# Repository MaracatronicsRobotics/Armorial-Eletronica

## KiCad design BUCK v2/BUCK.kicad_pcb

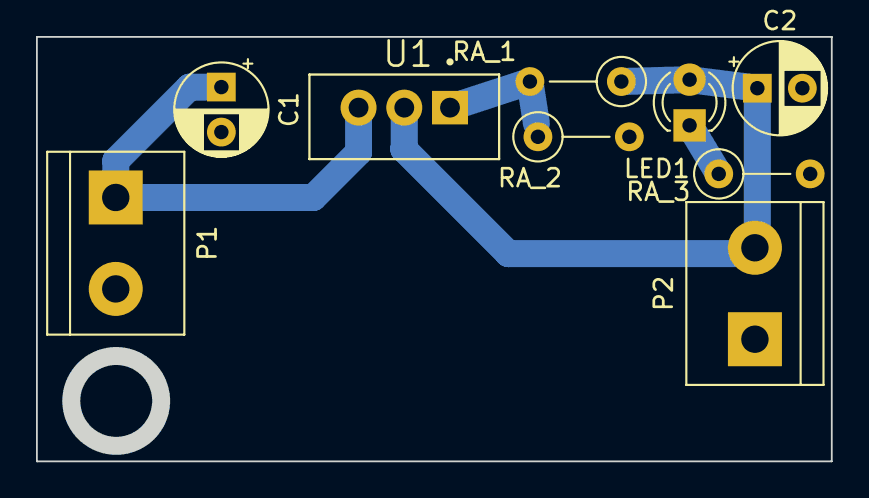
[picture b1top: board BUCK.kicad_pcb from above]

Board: 2 copper layers, 44.2 x 23.6 mm, 9 parts (0 on the bottom side), 5 nets.

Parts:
C1, C2: 100u; CP_Radial_D5.0mm_P2.50mm
LED1: LED; LED_D3.0mm
P1, P2: 282837-2; TerminalBlock_bornier-2_P5.08mm
RA_1: 220; R_Axial_DIN0207_L6.3mm_D2.5mm_P5.08mm_Vertical
RA_2: 1.2k; R_Axial_DIN0207_L6.3mm_D2.5mm_P5.08mm_Vertical
RA_3: 1k; R_Axial_DIN0207_L6.3mm_D2.5mm_P5.08mm_Vertical
U1: LM338T; TO254P1054X470X1955-3

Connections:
8V: C2.1, LED1.2 (A), P2.2, RA_1.1, U1.2 (VOUT)
18V: C1.1, P1.1, U1.3 (VIN)
GND: C1.2, C2.2, P1.2, P2.1, RA_2.2, RA_3.2
unnamed: LED1.1 (K), RA_3.1
unnamed: RA_1.2, RA_2.1, U1.1 (ADJ)

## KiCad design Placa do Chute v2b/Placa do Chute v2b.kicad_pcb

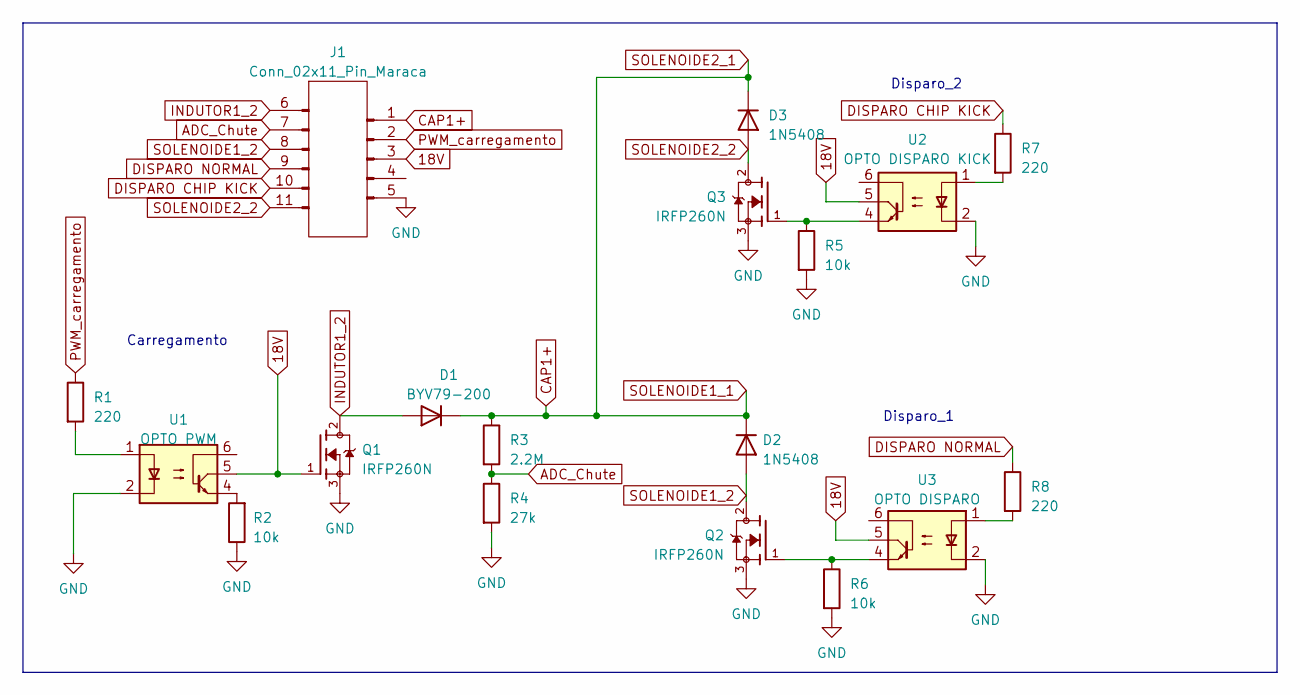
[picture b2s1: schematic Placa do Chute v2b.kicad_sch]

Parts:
D1: BYV79-200; TO-220-2_Vertical
D2, D3: 1N5408; D_DO-201AD_P15.24mm_Horizontal
J1: Conn_02x11_Pin_Maraca; Conn_2x11_Maraca_Chute
Q1, Q2, Q3: IRFP260N; TO545P1560X500X2460-3 90d; PARTREV 08/18/10
R1, R7, R8: 220; R_Axial_DIN0207_L6.3mm_D2.5mm_P10.16mm_Horizontal
R2, R5, R6: 10k; R_Axial_DIN0207_L6.3mm_D2.5mm_P10.16mm_Horizontal
R3: 2.2M; R_Axial_DIN0207_L6.3mm_D2.5mm_P10.16mm_Horizontal
R4: 27k; R_Axial_DIN0207_L6.3mm_D2.5mm_P10.16mm_Horizontal
U1: OPTO PWM; DIP-6_W7.62mm
U2: OPTO DISPARO KICK; DIP-6_W7.62mm
U3: OPTO DISPARO; DIP-6_W7.62mm

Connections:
18V: J1.3, Q1.1, U1.5, U2.5, U3.5
ADC_Chute: J1.7, R3.2, R4.1
CAP1+: D1.1 (K), D2.1 (K), D3.1 (K), J1.1, R3.1
DISPARO CHIP KICK: J1.10, R7.1
DISPARO NORMAL: J1.9, R8.1
GND: J1.5, Q1.3, Q2.3, Q3.3, R2.1, R4.2, R5.2, R6.2, U1.2, U2.2, U3.2
INDUTOR1_2: D1.2 (A), J1.6, Q1.2
unnamed: Q2.1, R6.1, U3.4
unnamed: Q3.1, R5.1, U2.4
unnamed: R1.2, U1.1
unnamed: R2.2, U1.4
unnamed: R7.2, U2.1
unnamed: R8.2, U3.1
PWM_carregamento: J1.2, R1.1
SOLENOIDE1_2: D2.2 (A), J1.8, Q2.2
SOLENOIDE2_2: D3.2 (A), J1.11, Q3.2

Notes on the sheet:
Disparo_2
Carregamento
Disparo_1

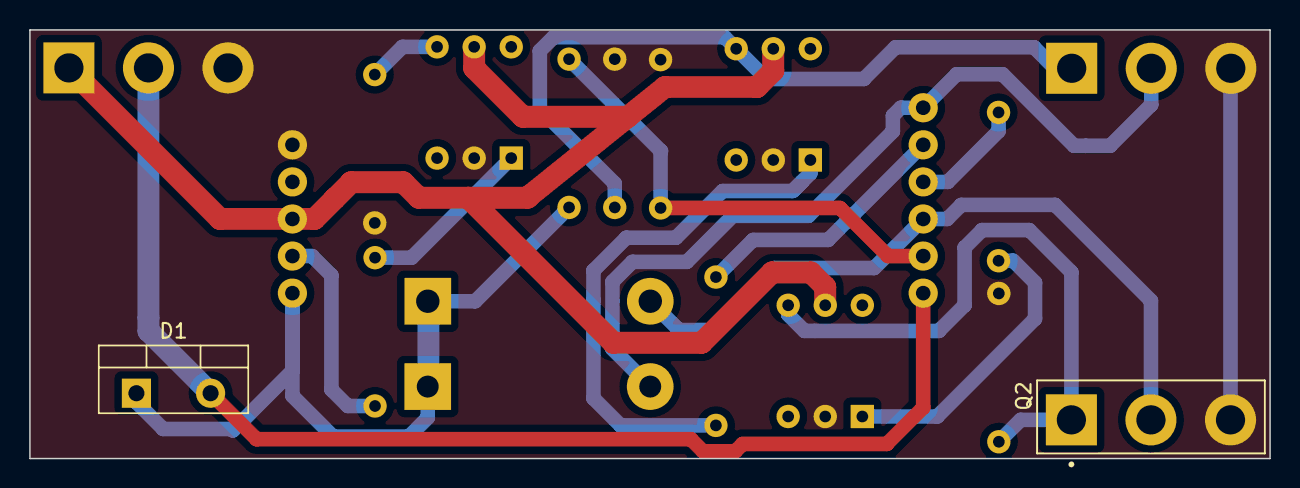
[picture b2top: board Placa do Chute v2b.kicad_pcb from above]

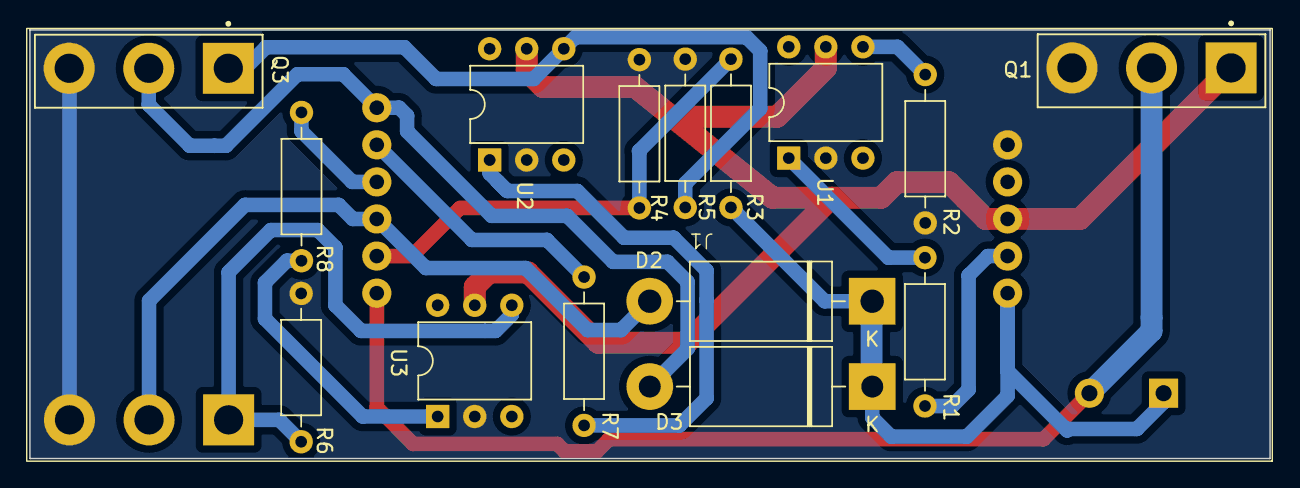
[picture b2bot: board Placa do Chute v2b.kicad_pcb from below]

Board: 2 copper layers, 84.9 x 29.4 mm, 18 parts (16 on the bottom side), 16 nets.

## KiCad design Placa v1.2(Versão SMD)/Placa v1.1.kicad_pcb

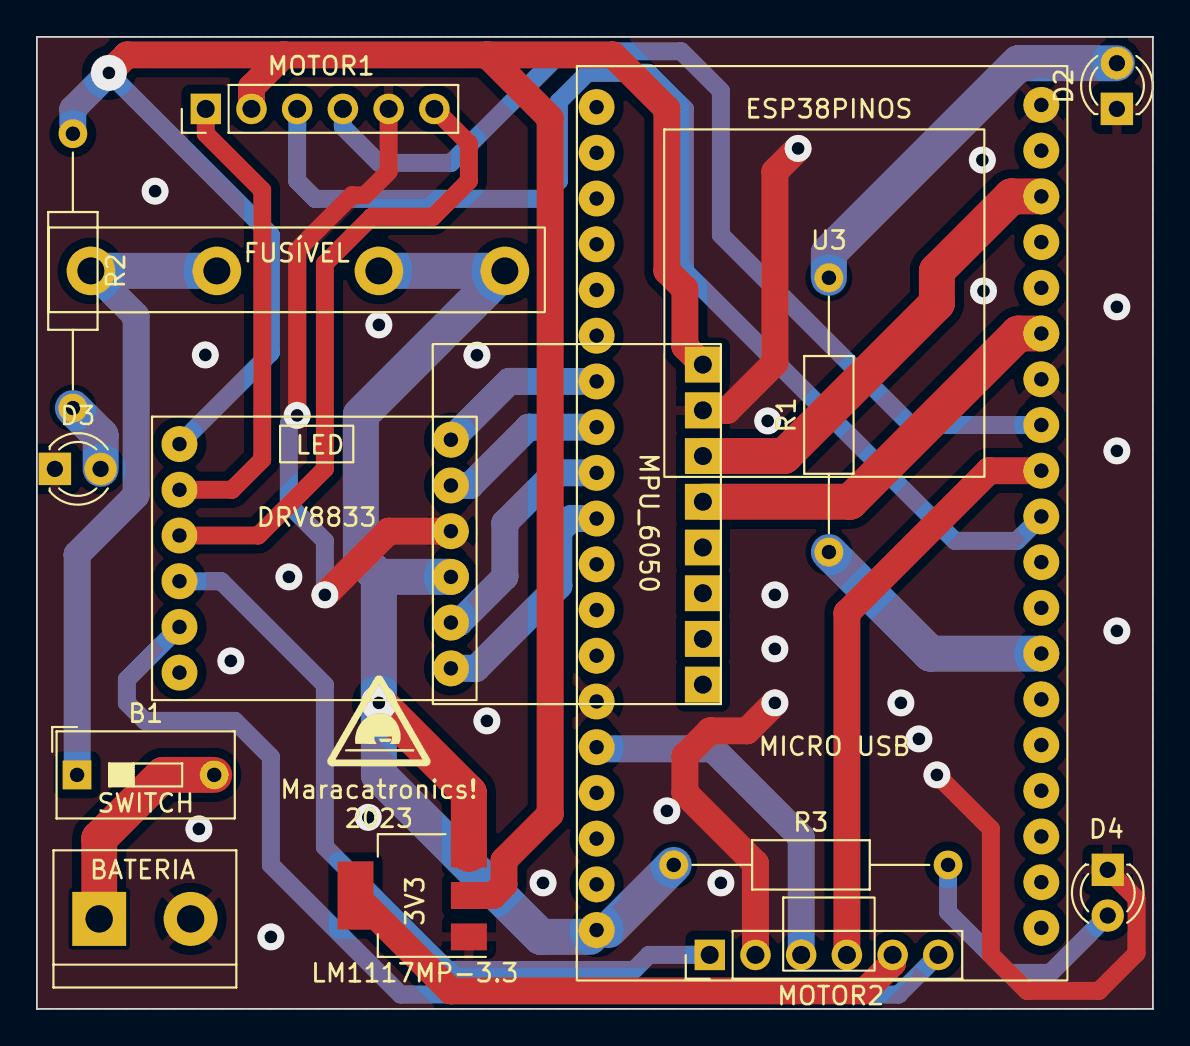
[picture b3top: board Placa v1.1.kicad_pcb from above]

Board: 2 copper layers, 62.0 x 54.0 mm, 15 parts (0 on the bottom side), 21 nets.

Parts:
3V3: LM1117MP-3.3; SOT-223-3_TabPin2
B1: SWITCH; SW_DIP_SPSTx01_Slide_9.78x4.72mm_W7.62mm_P2.54mm
BATERIA: Conn_01x02_Male; TerminalBlock_bornier-2_P5.08mm
D2, D3, D4: LED; LED_D3.0mm
DRV8833: DRV8833
FUSÍVEL: Fusivel; FUSIVEL
MOTOR1, MOTOR2: Conn_01x06_Male; PinHeader_1x06_P2.54mm_Vertical
MPU6050: MPU_6050; MPU 6050
R1, R2, R3: R_US; R_Axial_DIN0207_L6.3mm_D2.5mm_P15.24mm_Horizontal
U3: ESP38PINOS; ESP 38 PINOS

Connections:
3v3: 3V3.2 (VO), DRV8833.A0 (EEP), MOTOR1.2, MOTOR2.5, MPU6050.A0 (VCC), R2.1
7.4V: 3V3.3 (VI), B1.1, DRV8833.A9 (VCC), FUSÍVEL.A1, FUSÍVEL.A2, FUSÍVEL.A3, FUSÍVEL.A4, R3.1, U3.A18 (5V)
C1_1: MOTOR1.3, U3.A28 (G5)
C1_2: MOTOR2.4, U3.A27 (G18)
C2_1: MOTOR1.4, U3.A26 (G19)
C2_2: MOTOR2.3, U3.A14 (G13)
Earth: 3V3.1 (GND), BATERIA.2, D2.1 (K), D3.1 (K), D4.1 (K), DRV8833.A8 (GND), MOTOR1.5, MOTOR2.2, MPU6050.A1 (GND), U3.A13 (GND), U3.A19 (GND), U3.A25 (GND)
IN1: DRV8833.A11 (IN1), U3.A9 (G26)
IN2: DRV8833.A10 (IN2), U3.A8 (G25)
IN3: DRV8833.A7 (IN3), U3.A7 (G33)
IN4: DRV8833.A6 (IN4), U3.A6 (G32)
LED: R1.1, U3.A31 (G4)
unnamed: D2.2 (A), R1.2
unnamed: D3.2 (A), R2.2
unnamed: D4.2 (A), R3.2
SAIDA 1 PONTE H: DRV8833.A1 (OUT1), MOTOR1.1
SAIDA 2 PONTE H: DRV8833.A2 (OUT2), MOTOR1.6
SAIDA 3 PONTE H: DRV8833.A4 (OUT4), MOTOR2.6
SAIDA 4 PONTE H: DRV8833.A3 (OUT3), MOTOR2.1
SCL: MPU6050.A2 (SCL), U3.A21 (G22)
SDA: MPU6050.A3 (SDA), U3.A24 (G21)

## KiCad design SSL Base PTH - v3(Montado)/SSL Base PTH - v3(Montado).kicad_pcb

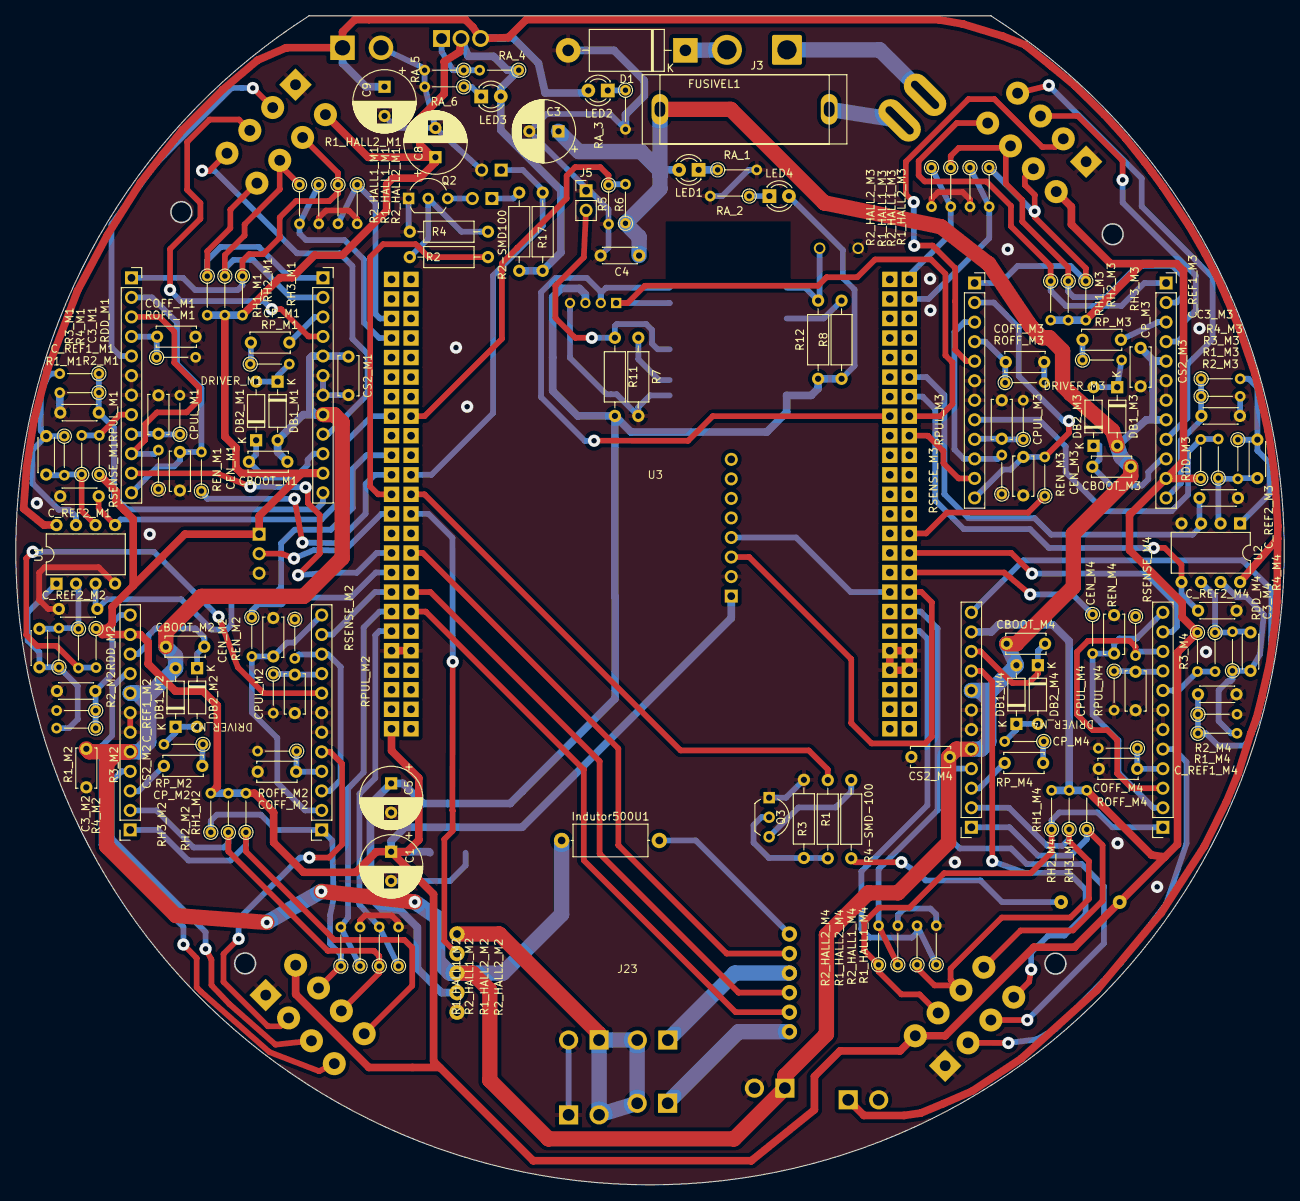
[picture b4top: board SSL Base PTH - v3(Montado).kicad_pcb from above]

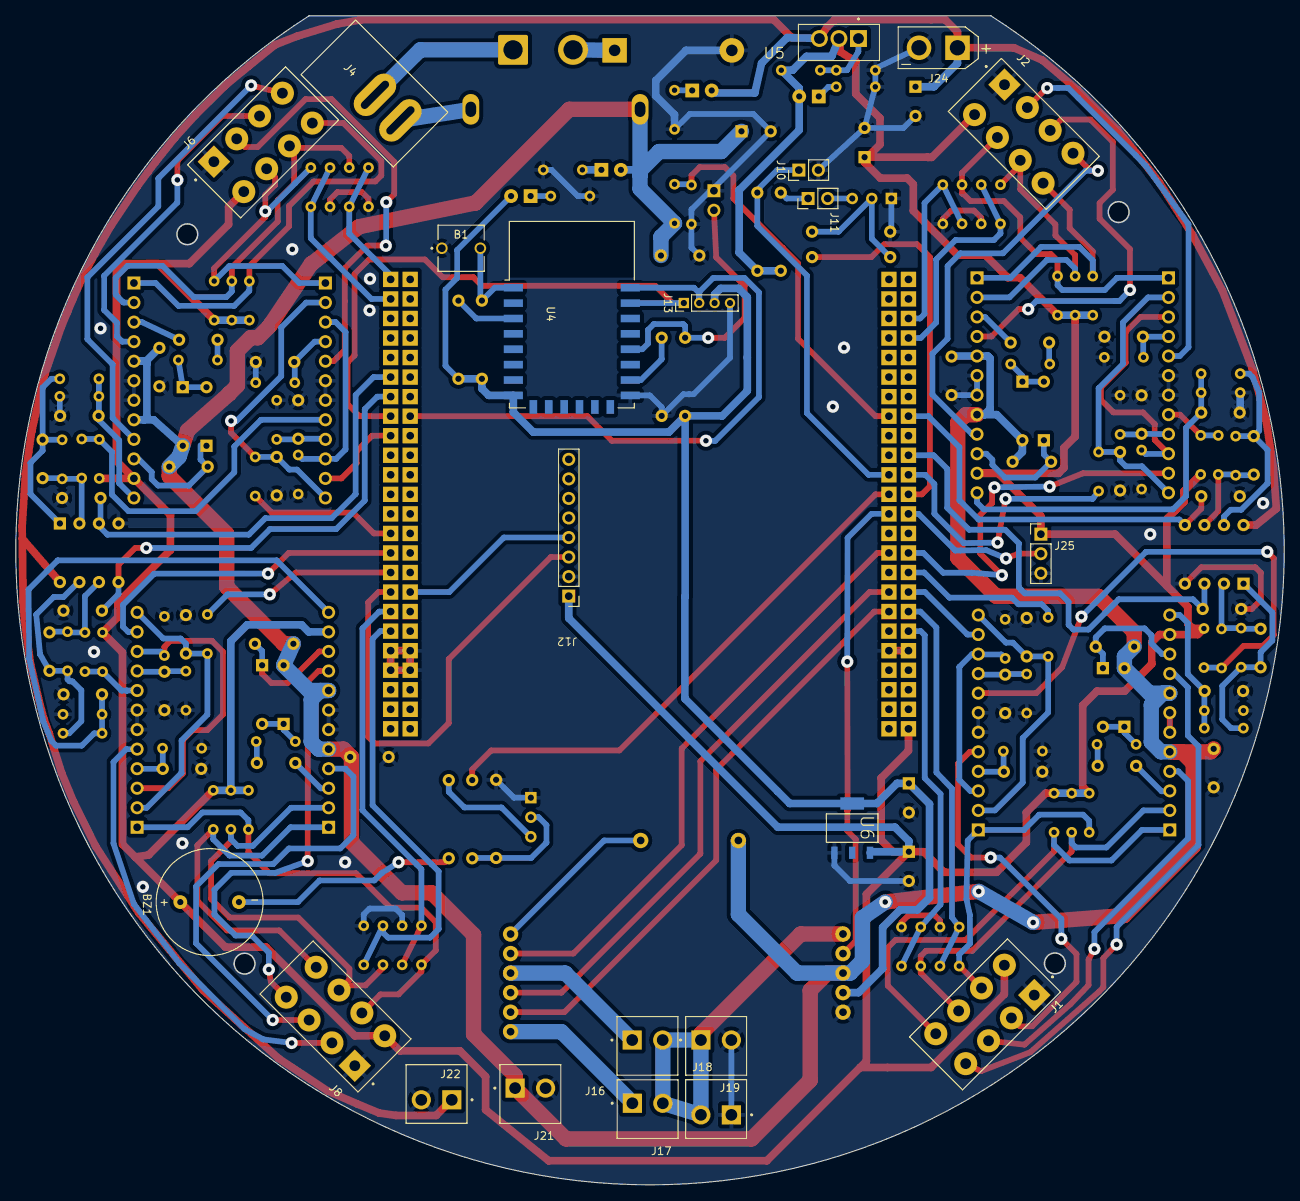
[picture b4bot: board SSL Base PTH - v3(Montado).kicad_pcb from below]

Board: 2 copper layers, 164.9 x 152.0 mm, 178 parts (22 on the bottom side), 132 nets.

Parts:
B1: BUTT-2; SW_BUTT-2
BZ1: Buzzer; XDCR_CPI-137-12T
C1: 10u; CP_Radial_D8.0mm_P3.80mm
C3: 1000u; CP_Radial_D8.0mm_P3.80mm
C3_M1, C3_M2, C3_M3, C3_M4: 220n C1206; C_Disc_D4.3mm_W1.9mm_P5.00mm
C4: 100n; C_Disc_D4.3mm_W1.9mm_P5.00mm
C5, C8, C9: 100u; CP_Radial_D8.0mm_P3.80mm
CBOOT_M1, CBOOT_M2, CBOOT_M3, CBOOT_M4: 220n C0805; C_Disc_D5.0mm_W2.5mm_P5.00mm
CEN_M1, CEN_M2, CEN_M3, CEN_M4: 5,6n CL10B102KB8NNNC C0805; C_Disc_D5.0mm_W2.5mm_P5.00mm
COFF_M1, COFF_M2, COFF_M3, COFF_M4: 1n CL10B102KB8NNNC C0805; C_Disc_D5.0mm_W2.5mm_P5.00mm
CPUL_M1, CPUL_M2, CPUL_M3, CPUL_M4: 10n C0805; C_Disc_D5.0mm_W2.5mm_P5.00mm
CP_M1, CP_M2, CP_M3, CP_M4: 10n C0603; C_Disc_D5.0mm_W2.5mm_P5.00mm
CS2_M1, CS2_M2, CS2_M3, CS2_M4: 100n C0603; C_Disc_D5.0mm_W2.5mm_P5.00mm
C_REF1_M1, C_REF1_M2, C_REF1_M3, C_REF1_M4: 33n C0805; C_Disc_D4.3mm_W1.9mm_P5.00mm
C_REF2_M1, C_REF2_M2, C_REF2_M3, C_REF2_M4: 100n C0805; C_Disc_D4.3mm_W1.9mm_P5.00mm
D1: 1N5408; D_DO-201AD_P15.24mm_Horizontal
DB1_M1, DB1_M2, DB1_M3, DB1_M4, DB2_M1, DB2_M2, DB2_M3, DB2_M4: 1N4148; D_DO-35_SOD27_P7.62mm_Horizontal
DRIVER_M1, DRIVER_M2, DRIVER_M3, DRIVER_M4: L6235D; Adaptador L6235
FUSIVEL1: MC000827
Indutor500U1: L; L_Axial_L9.5mm_D4.0mm_P12.70mm_Horizontal_Fastron_SMCC
J1: CONECTOR MOTOR 2; TE_1586037-8
J2: CONECTOR MOTOR 1; TE_1586037-8
J3: Bateria; SolderWire-2sqmm_1x02_P7.8mm_D2mm_OD3.9mm
J4: INTERRUPTOR; E-SWITCH_Maraca
J5: SW2; PinHeader_1x02_P2.54mm_Vertical
J6: CONECTOR MOTOR 3; TE_1586037-8
J8: CONECTOR MOTOR 4; TE_1586037-8
J10: REC_INFRA; PinHeader_1x02_P2.54mm_Vertical
J11: EM_INFRA; PinHeader_1x02_P2.54mm_Vertical
J12: MPU1; Girócópio
J13: Conversor; PinHeader_1x04_P2.00mm_Vertical
J16: SOLENOIDE1; TE_640388-2
J17: SOLENOIDE2; TE_640388-2
J18: CAPACITOR_1; TE_640388-2
J19: CAPACITOR_2; TE_640388-2
J21: Entrada_Buck_5V; TE_640388-2
J22: Saida_Buck_5V; TE_640388-2
J23: Conn_02x11_Pin_Maraca; Conn_2x11_Maraca_Chute_Placa
J24: XT30PB - ESC_DRIBLE_POWER; AMASS_XT30UPB-F_1x02_P5.0mm_Vertical
J25: JST 3 PIN - ESC; PinHeader_1x03_P2.54mm_Vertical
LED1, LED2, LED3, LED4: LED; LED_D3.0mm
Q2, Q3: 2N7000; TO-92_Inline_Wide
R1: 100 R_0603_1608; R_Axial_DIN0207_L6.3mm_D2.5mm_P10.16mm_Horizontal
R1_HALL1_M1, R1_HALL1_M2, R1_HALL1_M3, R1_HALL1_M4, R1_HALL2_M1, R1_HALL2_M2, R1_HALL2_M3, R1_HALL2_M4: 1k R_1206_3216; R_Axial_DIN0204_L3.6mm_D1.6mm_P5.08mm_Vertical
R1_M1, R1_M2, R1_M3, R1_M4: 22k R_2010_5025; R_Axial_DIN0204_L3.6mm_D1.6mm_P5.08mm_Vertical
R2: 100 R_0805_2012; R_Axial_DIN0207_L6.3mm_D2.5mm_P10.16mm_Horizontal
R2-SMD100, R4-SMD-100: R_1206_3216; R_Axial_DIN0207_L6.3mm_D2.5mm_P10.16mm_Horizontal
R2_HALL1_M1, R2_HALL1_M2, R2_HALL1_M3, R2_HALL1_M4, R2_HALL2_M1, R2_HALL2_M2, R2_HALL2_M3, R2_HALL2_M4: 1,6k R_1210_3225; R_Axial_DIN0204_L3.6mm_D1.6mm_P5.08mm_Vertical
R2_M1, R2_M2, R2_M3, R2_M4: 3,3K R_1206_3216; R_Axial_DIN0204_L3.6mm_D1.6mm_P5.08mm_Vertical
R3, R4, R7, R8, R11, R12: 10k R_0805_2012; R_Axial_DIN0207_L6.3mm_D2.5mm_P10.16mm_Horizontal
R3_M1, R3_M2, R3_M3, R3_M4: 4,7k R_1206_3216; R_Axial_DIN0204_L3.6mm_D1.6mm_P5.08mm_Vertical
R4_M1, R4_M2, R4_M3, R4_M4: 1M R_0805_2012; R_Axial_DIN0204_L3.6mm_D1.6mm_P5.08mm_Vertical
R5: 10M; R_Axial_DIN0204_L3.6mm_D1.6mm_P5.08mm_Vertical
R6: 3M; R_Axial_DIN0204_L3.6mm_D1.6mm_P5.08mm_Vertical
R17: R_0603_1608; R_Axial_DIN0207_L6.3mm_D2.5mm_P10.16mm_Horizontal
RA_1, RA_2, RA_3, RA_6: 270; R_Axial_DIN0204_L3.6mm_D1.6mm_P5.08mm_Vertical
RA_4: 1k; R_Axial_DIN0204_L3.6mm_D1.6mm_P5.08mm_Vertical
RA_5: 3,3k; R_Axial_DIN0204_L3.6mm_D1.6mm_P5.08mm_Vertical
RDD_M1, RDD_M2, RDD_M3, RDD_M4: 1k R_2010_5025; R_Axial_DIN0204_L3.6mm_D1.6mm_P5.08mm_Vertical
REN_M1, REN_M2, REN_M3, REN_M4: 100k R_0805_2012; R_Axial_DIN0204_L3.6mm_D1.6mm_P5.08mm_Vertical
RH1_M1, RH1_M2, RH1_M3, RH1_M4, RH2_M1, RH2_M2, RH2_M3, RH2_M4, RH3_M1, RH3_M2, RH3_M3, RH3_M4: 10k R_0805_2012; R_Axial_DIN0204_L3.6mm_D1.6mm_P5.08mm_Vertical
ROFF_M1, ROFF_M2, ROFF_M3, ROFF_M4: 33k R_0805_2012; R_Axial_DIN0204_L3.6mm_D1.6mm_P5.08mm_Vertical
RPUL_M1, RPUL_M2, RPUL_M3, RPUL_M4: 47k R_0805_2012; R_Axial_DIN0204_L3.6mm_D1.6mm_P5.08mm_Vertical
RP_M1, RP_M2, RP_M3, RP_M4: 100 R_0805_2012; R_Axial_DIN0204_L3.6mm_D1.6mm_P5.08mm_Vertical
RSENSE_M1, RSENSE_M2, RSENSE_M3, RSENSE_M4: 0,3; R_Axial_DIN0204_L3.6mm_D1.6mm_P5.08mm_Vertical
U1: AMPOP_LOCO1_M12 LM358; DIP-8_W7.62mm
U2: AMPOP_LOCO1_M34 LM358; DIP-8_W7.62mm
U3: STM32F401VETx; STM32MARACA_3D
U4: ESP-12E
U5: LM338T; TO254P1054X470X1955-3
U6: LM1117MP-3.3; SOT230P696X180-4N

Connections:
3,3V: C5.1, J13.3, J23.4, LED4.2 (A), R8.1, R11.2, R12.1, U4.8 (VCC), U6.4 (VOUT)
5V: BZ1.1 (-), C1.1, C8.1, DRIVER_M1.14 (BRAKE), DRIVER_M2.14 (BRAKE), DRIVER_M3.14 (BRAKE), DRIVER_M4.14 (BRAKE), J1.2, J2.2, J6.2, J8.2, J12.1, J25.1, LED3.2 (A), R2-SMD100.2, R17.1, RA_4.1, RDD_M1.1, RDD_M2.1, RDD_M3.1, RDD_M4.1, RH1_M1.2, RH1_M2.2, RH1_M3.2, RH1_M4.2, RH2_M1.2, RH2_M2.2, RH2_M3.2, RH2_M4.2, RH3_M1.2, RH3_M2.2, RH3_M3.2, RH3_M4.2, U3.96 (+5V_(1)), U5.2 (VOUT), U6.3 (IN)
8V: C9.1, J22.1, J24.1, LED2.2 (A), U1.8 (V+), U2.8 (V+), U5.3 (VIN)
18V: C3.1, C4.1, CBOOT_M1.1, CBOOT_M2.1, CBOOT_M3.1, CBOOT_M4.1, CS2_M1.1, CS2_M2.1, CS2_M3.1, CS2_M4.1, DB1_M1.2 (A), DB1_M2.2 (A), DB1_M3.2 (A), DB1_M4.2 (A), DRIVER_M1.17 (VSB), DRIVER_M1.20 (VSA), DRIVER_M2.17 (VSB), DRIVER_M2.20 (VSA), DRIVER_M3.17 (VSB), DRIVER_M3.20 (VSA), DRIVER_M4.17 (VSB), DRIVER_M4.20 (VSA), FUSIVEL1.P$2, Indutor500U1.1, J21.1, J23.3, LED1.2 (A), R5.1
ADC_Chute: J23.7, U3.63 (PC_3)
BAT_NEG: D1.1 (K), J3.2
BAT_POS: J3.1, J4.2
Buzzer: R1.1, U3.60 (PA_3)
CAP1+: J16.2, J17.2, J18.2, J19.1, J23.1
DIAG/EN_M1: CEN_M1.1, DRIVER_M1.2 (DIAG), DRIVER_M1.12 (EN), REN_M1.2
DIAG/EN_M2: CEN_M2.1, DRIVER_M2.2 (DIAG), DRIVER_M2.12 (EN), REN_M2.2
DIAG/EN_M3: CEN_M3.1, DRIVER_M3.2 (DIAG), DRIVER_M3.12 (EN), REN_M3.2
DIAG/EN_M4: CEN_M4.1, DRIVER_M4.2 (DIAG), DRIVER_M4.12 (EN), REN_M4.2
DISPARO CHIP KICK: J23.10, U3.66 (PE_5)
DISPARO NORMAL: J23.9, U3.65 (PC_13)
DRIBLE: J25.2, U3.85 (PA_0)
EN_M1: REN_M1.1, U3.83 (PA_4)
EN_M2: REN_M2.1, U3.88 (PC_0)
EN_M3: REN_M3.1, U3.14 (PD_4)
EN_M4: REN_M4.1, U3.16 (PB_3)
FWD/REV_M1: DRIVER_M1.11 (FWD/REV), U3.87 (PC_2)
FWD/REV_M2: DRIVER_M2.11 (FWD/REV), U3.89 (PE_6)
FWD/REV_M3: DRIVER_M3.11 (FWD/REV), U3.9 (PA_11)
FWD/REV_M4: DRIVER_M4.11 (FWD/REV), U3.15 (PD_6)
GND: B1.1, C1.2, C3.2, C4.2, C5.2, C8.2, C9.2, CEN_M1.2, CEN_M2.2, CEN_M3.2, CEN_M4.2, COFF_M1.2, COFF_M2.2, COFF_M3.2, COFF_M4.2, CPUL_M1.2, CPUL_M2.2, CPUL_M3.2, CPUL_M4.2, CS2_M1.2, CS2_M2.2, CS2_M3.2, CS2_M4.2, C_REF1_M1.2, C_REF1_M2.2, C_REF1_M3.2, C_REF1_M4.2, C_REF2_M1.2, C_REF2_M2.2, C_REF2_M3.2, C_REF2_M4.2, D1.2 (A), DRIVER_M1.6 (GND), DRIVER_M1.7 (GND), DRIVER_M1.18 (GND), DRIVER_M1.19 (GND), DRIVER_M2.6 (GND), DRIVER_M2.7 (GND), DRIVER_M2.18 (GND), DRIVER_M2.19 (GND), DRIVER_M3.6 (GND), DRIVER_M3.7 (GND), DRIVER_M3.18 (GND), DRIVER_M3.19 (GND), DRIVER_M4.6 (GND), DRIVER_M4.7 (GND), DRIVER_M4.18 (GND), DRIVER_M4.19 (GND), J1.1, J2.1, J5.1, J6.1, J8.1, J10.2, J12.2, J13.4, J18.1, J19.2, J21.2, J22.2, J23.5, J24.2, J25.3, Q2.1 (S), Q3.1 (S), R2_HALL1_M1.2, R2_HALL1_M2.2, R2_HALL1_M3.2, R2_HALL1_M4.2, R2_HALL2_M1.2, R2_HALL2_M2.2, R2_HALL2_M3.2, R2_HALL2_M4.2, R2_M1.2, R2_M2.2, R2_M3.2, R2_M4.2, R3.2, R4.2, R6.2, R7.2, RA_1.2, RA_2.2, RA_3.2, RA_5.2, RA_6.2, ROFF_M1.2, ROFF_M2.2, ROFF_M3.2, ROFF_M4.2, RPUL_M1.2, RPUL_M2.2, RPUL_M3.2, RPUL_M4.2, RSENSE_M1.1, RSENSE_M2.1, RSENSE_M3.1, RSENSE_M4.1, U1.4 (V-), U2.4 (V-), U3.20 (GND_(6)), U3.21 (GND_(5)), U3.44 (GND_(4)), U3.45 (GND_(3)), U3.68 (GND_(2)), U3.92 (GND_(1)), U4.15 (GND), U6.1 (ADJ/GND)
H1_M1: R1_HALL1_M1.2, R2_HALL1_M1.1, U3.75 (PE_15)
H1_M2: R1_HALL1_M2.2, R2_HALL1_M2.1, U3.90 (PE_4)
H1_M3: R1_HALL1_M3.2, R2_HALL1_M3.1, U3.2 (PD_9)
H1_M4: R1_HALL1_M4.2, R2_HALL1_M4.1, U3.18 (PB_8)
H2_M1: R1_HALL2_M1.2, R2_HALL2_M1.1, U3.76 (PE_13)
H2_M2: R1_HALL2_M2.2, R2_HALL2_M2.1, U3.91 (PE_2)
H2_M3: R1_HALL2_M3.2, R2_HALL2_M3.1, U3.1 (PB_15)
H2_M4: R1_HALL2_M4.2, R2_HALL2_M4.1, U3.19 (PE_0)
HALL1_M1: DRIVER_M1.1 (H1), J2.4, R1_HALL1_M1.1, RH1_M1.1
HALL1_M2: DRIVER_M2.1 (H1), J1.4, R1_HALL1_M2.1, RH1_M2.1
HALL1_M3: DRIVER_M3.1 (H1), J6.4, R1_HALL1_M3.1, RH1_M3.1
HALL1_M4: DRIVER_M4.1 (H1), J8.4, R1_HALL1_M4.1, RH1_M4.1
HALL2_M1: DRIVER_M1.23 (H2), J2.6, R1_HALL2_M1.1, RH2_M1.1
HALL2_M2: DRIVER_M2.23 (H2), J1.6, R1_HALL2_M2.1, RH2_M2.1
HALL2_M3: DRIVER_M3.23 (H2), J6.6, R1_HALL2_M3.1, RH2_M3.1
HALL2_M4: DRIVER_M4.23 (H2), J8.6, R1_HALL2_M4.1, RH2_M4.1
HALL3_M1: DRIVER_M1.24 (H3), J2.8, RH3_M1.1
HALL3_M2: DRIVER_M2.24 (H3), J1.8, RH3_M2.1
HALL3_M3: DRIVER_M3.24 (H3), J6.8, RH3_M3.1
HALL3_M4: DRIVER_M4.24 (H3), J8.8, RH3_M4.1
INFRA: J10.1, R17.2, U3.59 (PA_5)
IO0: J5.2, R11.1, U4.18 (GPIO0)
IR PWM: R2.2, U3.84 (PA_2)
Indutor: Indutor500U1.2, J23.6
LEITURA_BATERIA: R5.2, R6.1, U3.56 (PB_1)
MOTOR1_1: DRIVER_M1.5 (OUT1), J2.3
MOTOR1_2: DRIVER_M1.21 (OUT2), J2.5
MOTOR1_3: DRIVER_M1.16 (OUT3), J2.7
MOTOR2_1: DRIVER_M2.5 (OUT1), J1.3
MOTOR2_2: DRIVER_M2.21 (OUT2), J1.5
MOTOR2_3: DRIVER_M2.16 (OUT3), J1.7
MOTOR3_1: DRIVER_M3.5 (OUT1), J6.3
MOTOR3_2: DRIVER_M3.21 (OUT2), J6.5
MOTOR3_3: DRIVER_M3.16 (OUT3), J6.7
MOTOR4_1: DRIVER_M4.5 (OUT1), J8.3
MOTOR4_2: DRIVER_M4.21 (OUT2), J8.5
MOTOR4_3: DRIVER_M4.16 (OUT3), J8.7
unnamed: BZ1.2 (+), R4-SMD-100.2
unnamed: C3_M1.1, R4_M1.1, U1.7
unnamed: C3_M2.1, R4_M2.1, U1.1
unnamed: C3_M3.1, R4_M3.1, U2.1
unnamed: C3_M4.1, R4_M4.1, U2.7
unnamed: CP_M1.2, RP_M1.1
unnamed: CP_M2.2, RP_M2.1
unnamed: CP_M3.2, RP_M3.1
unnamed: CP_M4.2, RP_M4.1
unnamed: DB1_M1.1 (K), DB2_M1.2 (A), RP_M1.2
unnamed: DB1_M2.1 (K), DB2_M2.2 (A), RP_M2.2
unnamed: DB1_M3.1 (K), DB2_M3.2 (A), RP_M3.2
unnamed: DB1_M4.1 (K), DB2_M4.2 (A), RP_M4.2
unnamed: FUSIVEL1.P$1, J4.1
unnamed: J11.1, R2-SMD100.1
unnamed: J11.2, Q2.3 (D)
unnamed: LED1.1 (K), RA_1.1
unnamed: LED2.1 (K), RA_3.1
unnamed: LED3.1 (K), RA_6.1
unnamed: LED4.1 (K), RA_2.1
unnamed: Q2.2 (G), R2.1, R4.1
unnamed: Q3.3 (D), R4-SMD-100.1
unnamed: Q3.2 (G), R1.2, R3.1
unnamed: C3_M2.2, R3_M2.1, R4_M2.2, U1.2 (-)
unnamed: C3_M1.2, R3_M1.1, R4_M1.2, U1.6 (-)
unnamed: C3_M3.2, R3_M3.1, R4_M3.2, U2.2 (-)
unnamed: C3_M4.2, R3_M4.1, R4_M4.2, U2.6 (-)
unnamed: R8.2, U4.3 (EN)
unnamed: R7.1, U4.16 (GPIO15)
unnamed: B1.2, R12.2, U4.1 (~RST)
unnamed: RA_4.2, RA_5.1, U5.1 (ADJ)
PWM_Carregamento: J23.2, U3.61 (PA_1)
PWM_RODA_1: C_REF2_M1.1, R1_M1.2, U1.5 (+), U3.80 (PB_0)
PWM_RODA_2: C_REF2_M2.1, R1_M2.2, U1.3 (+), U3.82 (PA_6)
PWM_RODA_3: C_REF2_M3.1, R1_M3.2, U2.3 (+), U3.6 (PC_7)
PWM_RODA_4: C_REF2_M4.1, R1_M4.2, U2.5 (+), U3.7 (PC_9)
RCOFF_M1: COFF_M1.1, DRIVER_M1.4 (RCOFF), ROFF_M1.1
RCOFF_M2: COFF_M2.1, DRIVER_M2.4 (RCOFF), ROFF_M2.1
RCOFF_M3: COFF_M3.1, DRIVER_M3.4 (RCOFF), ROFF_M3.1
RCOFF_M4: COFF_M4.1, DRIVER_M4.4 (RCOFF), ROFF_M4.1
RCPULSE_M1: CPUL_M1.1, DRIVER_M1.9 (RCPULSE), RPUL_M1.1
RCPULSE_M2: CPUL_M2.1, DRIVER_M2.9 (RCPULSE), RPUL_M2.1
RCPULSE_M3: CPUL_M3.1, DRIVER_M3.9 (RCPULSE), RPUL_M3.1
RCPULSE_M4: CPUL_M4.1, DRIVER_M4.9 (RCPULSE), RPUL_M4.1
RX_STM: J13.2, U3.32 (PA_10), U4.22 (GPIO1/TXD)
SCL: J12.3, U3.17 (PB_6)
SDA: J12.4, U3.41 (PB_7)
SENSE_M1: DRIVER_M1.3 (SENSEA), DRIVER_M1.10 (SENSEB), RSENSE_M1.2
SENSE_M2: DRIVER_M2.3 (SENSEA), DRIVER_M2.10 (SENSEB), RSENSE_M2.2
SENSE_M3: DRIVER_M3.3 (SENSEA), DRIVER_M3.10 (SENSEB), RSENSE_M3.2
SENSE_M4: DRIVER_M4.3 (SENSEA), DRIVER_M4.10 (SENSEB), RSENSE_M4.2
SOLENOIDE_1_1: J16.1, J23.8
SOLENOIDE_2_1: J17.1, J23.11
TACHO_M1: DRIVER_M1.8 (TACHO), R3_M1.2, RDD_M1.2
TACHO_M2: DRIVER_M2.8 (TACHO), R3_M2.2, RDD_M2.2
TACHO_M3: DRIVER_M3.8 (TACHO), R3_M3.2, RDD_M3.2
TACHO_M4: DRIVER_M4.8 (TACHO), R3_M4.2, RDD_M4.2
TX_STM: J13.1, U3.8 (PA_9), U4.21 (GPIO3/RXD)
VBOOT_M1: CBOOT_M1.2, DB2_M1.1 (K), DRIVER_M1.15 (VBOOT)
VBOOT_M2: CBOOT_M2.2, DB2_M2.1 (K), DRIVER_M2.15 (VBOOT)
VBOOT_M3: CBOOT_M3.2, DB2_M3.1 (K), DRIVER_M3.15 (VBOOT)
VBOOT_M4: CBOOT_M4.2, DB2_M4.1 (K), DRIVER_M4.15 (VBOOT)
VCP_M1: CP_M1.1, DRIVER_M1.22 (VCP)
VCP_M2: CP_M2.1, DRIVER_M2.22 (VCP)
VCP_M3: CP_M3.1, DRIVER_M3.22 (VCP)
VCP_M4: CP_M4.1, DRIVER_M4.22 (VCP)
VREF_M1: C_REF1_M1.1, DRIVER_M1.13 (VREF), R1_M1.1, R2_M1.1
VREF_M2: C_REF1_M2.1, DRIVER_M2.13 (VREF), R1_M2.1, R2_M2.1
VREF_M3: C_REF1_M3.1, DRIVER_M3.13 (VREF), R1_M3.1, R2_M3.1
VREF_M4: C_REF1_M4.1, DRIVER_M4.13 (VREF), R1_M4.1, R2_M4.1
